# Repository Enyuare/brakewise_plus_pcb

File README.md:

# BrakeWise Plus — Phase 1 PCB

PCB board design for **Phase 1 of the BrakeWise Plus Tool** (ATI brake tread body board), designed in KiCad.

> ⚠️ **Work in progress — not complete.**
> This board is still in the design phase. The schematic and layout are not finalized,
> have not been reviewed.

## Board size

| | Width | Height | Area |
|---|---|---|---|
| **mm** | 33.325 mm | 34.65 mm | ≈ 1154.71 mm² |
| **inches** | ≈ 1.312 in | ≈ 1.364 in | ≈ 1.790 in² |

> Note: the board is still in the design phase, so its dimensions and area may change.

## Key components

| Ref | Part | Function |
|-----|------|----------|
| U3 | STM32U575CIUx (QFN-48) | Main microcontroller |
| U6 | CH334F (QFN-24) | USB 2.0 hub controller |
| U4 | AS5304A-ATSM (TSSOP-20) | Magnetic encoder |
| U5 | SN74LVC3G17DCUR (VSSOP-8) | Triple Schmitt-trigger buffer |
| U2 | AP2112K-3.3 | 3.3 V LDO regulator |
| — | TPS630701RNMR | Buck-boost converter (in schematic) |
| Q1 | AO3401A (SOT-23) | P-channel MOSFET |
| L1 | 1.5 µH (Coilcraft XxL4020) | Power inductor |
| J1 | USB-C receptacle (USB 2.0) | USB connection |
| J2–J6 | JST GH connectors (4/5/6-pin) | External connections |
| Y1, Y2 | 3.2 × 2.5 mm crystals (Y2: 12 MHz) | Clock sources |
| TP1, TP2 | 1.5 mm test pads | Test points |

Plus 0402/0603/0805 passives (R1–R11, C1–C12).

## Files

- `ATI_brake_tread_body.kicad_pro` — KiCad project
- `ATI_brake_tread_body.kicad_sch` — schematic
- `ATI_brake_tread_body.kicad_pcb` — board layout
- `Parts.kicad_sym` — custom symbol library

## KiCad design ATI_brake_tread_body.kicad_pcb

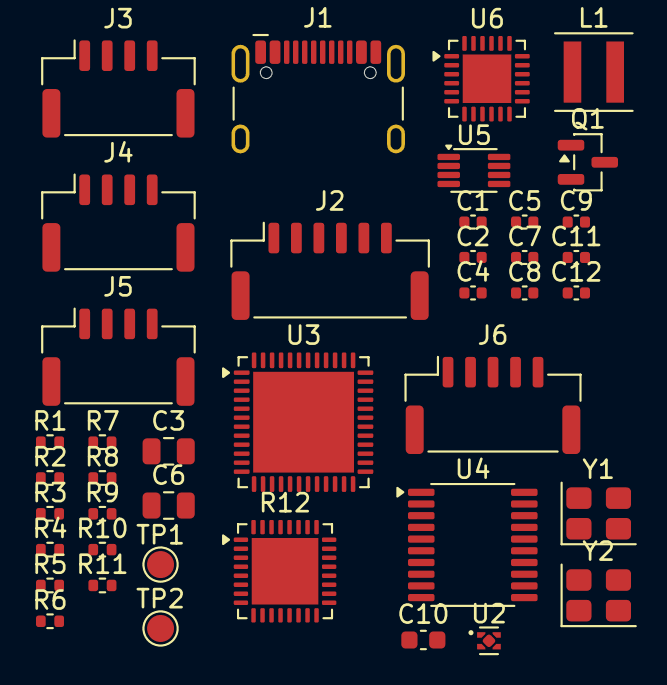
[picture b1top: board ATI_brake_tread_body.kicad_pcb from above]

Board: 2 copper layers, 41 parts (0 on the bottom side), 26 nets, no tracks yet.

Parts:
C1, C2: 1u; C_0402_1005Metric
C3: 22u; C_0805_2012Metric
C4: 100n; C_0402_1005Metric
C5: 5.787m; C_0402_1005Metric
C6: 47u; C_0805_2012Metric
C7: 1uF; C_0402_1005Metric
C8, C9: 0.1uF; C_0402_1005Metric
C10: 10uF; C_0603_1608Metric
C11, C12: 12p; C_0402_1005Metric
J1: USB_C_Receptacle_USB2.0_14P; USB_C_Receptacle_HCTL_HC-TYPE-C-16P-01A
J2: Conn_01x06; JST_GH_SM06B-GHS-TB_1x06-1MP_P1.25mm_Horizontal
J3, J4, J5: Conn_01x04; JST_GH_SM04B-GHS-TB_1x04-1MP_P1.25mm_Horizontal
J6: JST_PH_S5B; JST_GH_SM05B-GHS-TB_1x05-1MP_P1.25mm_Horizontal
L1: 1.5u; L_Coilcraft_XxL4020
Q1: AO3401A; SOT-23
R1, R9, R11: 10k; R_0402_1005Metric
R2, R3: 5.1k; R_0402_1005Metric
R4: 499k; R_0402_1005Metric
R5, R7: 22; R_0402_1005Metric
R6, R8: 100k; R_0402_1005Metric
R10: 100; R_0402_1005Metric
R12: 10k; QFN-32-1EP_5x5mm_P0.5mm_EP3.7x3.7mm
TP1, TP2: TestPoint; TestPoint_Pad_D1.5mm
U2: AP2112K-3.3; Texas_X2SON-4_1x1mm_P0.65mm
U3: STM32U575CIUx; QFN-48-1EP_7x7mm_P0.5mm_EP5.6x5.6mm
U4: AS5304A-ATSM; TSSOP-20_4.4x6.5mm_P0.65mm
U5: SN74LVC3G17DCUR; VSSOP-8_2.3x2mm_P0.5mm
U6: CH334F; QFN-24-1EP_4x4mm_P0.5mm_EP2.7x2.7mm
Y1: Crystal; Crystal_SMD_3225-4Pin_3.2x2.5mm
Y2: 12 Mhz; Crystal_SMD_3225-4Pin_3.2x2.5mm

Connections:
+5V: C1.1, C3.1, C9.1, C10.1, J1.A4 (VBUS), J1.A9 (VBUS), J1.B4 (VBUS), J1.B9 (VBUS), J6.4, R1.1, R9.1, U2.1 (VIN), U4.3 (VDDP), U4.7 (VDD), U4.16 (VDDA_Hall)
/A0: TP1.1 (1_1), U4.6 (A0)
/A5V: U4.2 (A), U5.1 (1A)
/B5V: U4.4 (B), U5.3 (2A)
/Ind5V: U4.8 (Index), U5.6 (3A)
A3V3: C2.1, C7.1, C8.1, J2.1, J3.3, J4.3, J5.3, J6.2, J6.3, Q1.3 (D), R11.2, U2.5 (VOUT), U3.1 (VBAT), U3.9 (VDDA), U3.24 (VDD), U3.36 (VDD), U3.48 (VDD), U5.5 (2Y), U5.7 (1Y), U5.8 (VCC), U6.19 (V5), U6.20 (VDD33_{LDO})
D2+: J2.4, U6.10 (DP2+)
D2-: J2.3, U6.9 (DM2-)
D+: R7.2, U6.15 (DPU+)
D-: R5.2, U6.14 (DMU-)
GND: C1.2, C2.2, C3.2, C4.2, C5.2, C6.2, C7.2, C8.2, C9.2, C10.2, C11.2, C12.2, J1.A1 (GND), J1.A12 (GND), J1.B1 (GND), J1.B12 (GND), J1.SH (SHIELD), J2.6, J3.2, J3.4, J4.2, J4.4, J5.2, J5.4, J6.1, R2.2, R3.2, R6.2, R12.1, U2.2 (GND), U4.1 (VSS), U4.15 (TEST_GND), U4.20 (ZPZmskdis), U5.4 (GND), U6.25 (GND)
Ind3V3: TP2.1 (1_1), U5.2 (3Y)
LED_PWR: J2.2, Q1.2 (S)
LSR: C5.1, C6.1, J2.5, R4.1, R8.1
unnamed: J1.A5 (CC1), R3.1
unnamed: J1.B5 (CC2), R2.1
unnamed: J1.A6 (D+), J1.B6 (D+), R7.1
unnamed: J1.A7 (D-), J1.B7 (D-), R5.1
unnamed: Q1.1 (G), R10.2, R11.1
unnamed: R4.2, R6.1
unnamed: R1.2, U2.3 (EN)
unnamed: U3.23 (VSS), U3.35 (VSS), U3.47 (VSS), U3.49 (VSS)
unnamed: U6.4 (XI), Y2.1
unnamed: U6.3 (XO), Y2.2
OSC_IN: C11.1, Y1.1
OSC_OUT: C12.1, Y1.2
